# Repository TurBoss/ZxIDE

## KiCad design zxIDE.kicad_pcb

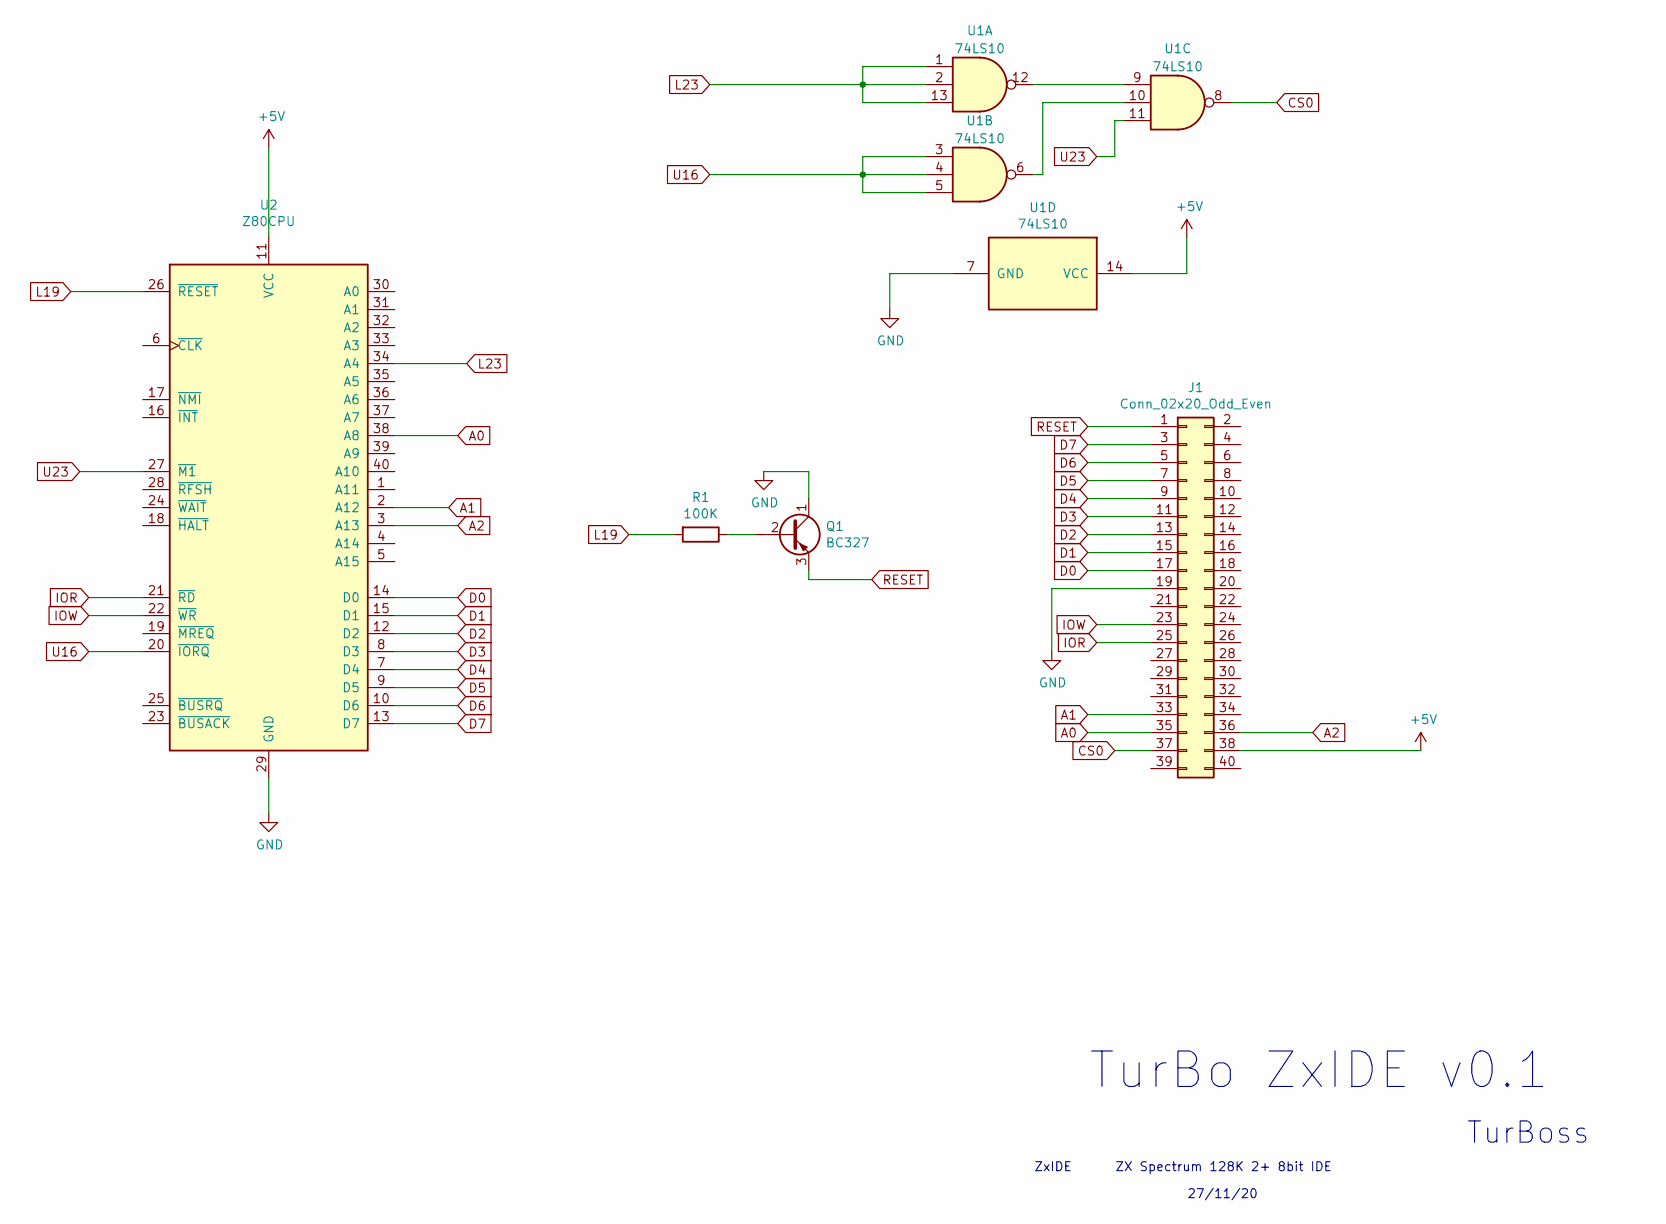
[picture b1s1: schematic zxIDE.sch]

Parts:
J1: Conn_02x20_Odd_Even; IDC-Header_2x20_P2.54mm_Vertical
Q1: BC327; TO-92_Inline
R1: 100K; R_Axial_DIN0207_L6.3mm_D2.5mm_P15.24mm_Horizontal
U1: 74LS10; DIP-14_W7.62mm_Socket_LongPads
U2: Z80CPU; DIP-40_W15.24mm_Socket_LongPads

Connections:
+5V: J1.38, U1.14 (VCC), U2.11 (VCC)
A0: J1.35, U2.38 (A8)
A1: J1.33, U2.2 (A12)
A2: J1.36, U2.3 (A13)
CS0: J1.37, U1.8
D0: J1.17, U2.14 (D0)
D1: J1.15, U2.15 (D1)
D2: J1.13, U2.12 (D2)
D3: J1.11, U2.8 (D3)
D4: J1.9, U2.7 (D4)
D5: J1.7, U2.9 (D5)
D6: J1.5, U2.10 (D6)
D7: J1.3, U2.13 (D7)
GND: J1.19, Q1.1 (C), U1.7 (GND), U2.29 (GND)
IOR: J1.25, U2.21 (~RD~)
IOW: J1.23, U2.22 (~WR~)
L19: R1.2, U2.26 (~RESET~)
L23: U1.1, U1.2, U1.13, U2.34 (A4)
unnamed: Q1.2 (B), R1.1
unnamed: U1.6, U1.10
unnamed: U1.9, U1.12
RESET: J1.1, Q1.3 (E)
U16: U1.3, U1.4, U1.5, U2.20 (~IORQ~)
U23: U1.11, U2.27 (~M1~)

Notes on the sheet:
TurBo ZxIDE v0.1
ZxIDE
27/11/20
TurBoss
ZX Spectrum 128K 2+ 8bit IDE

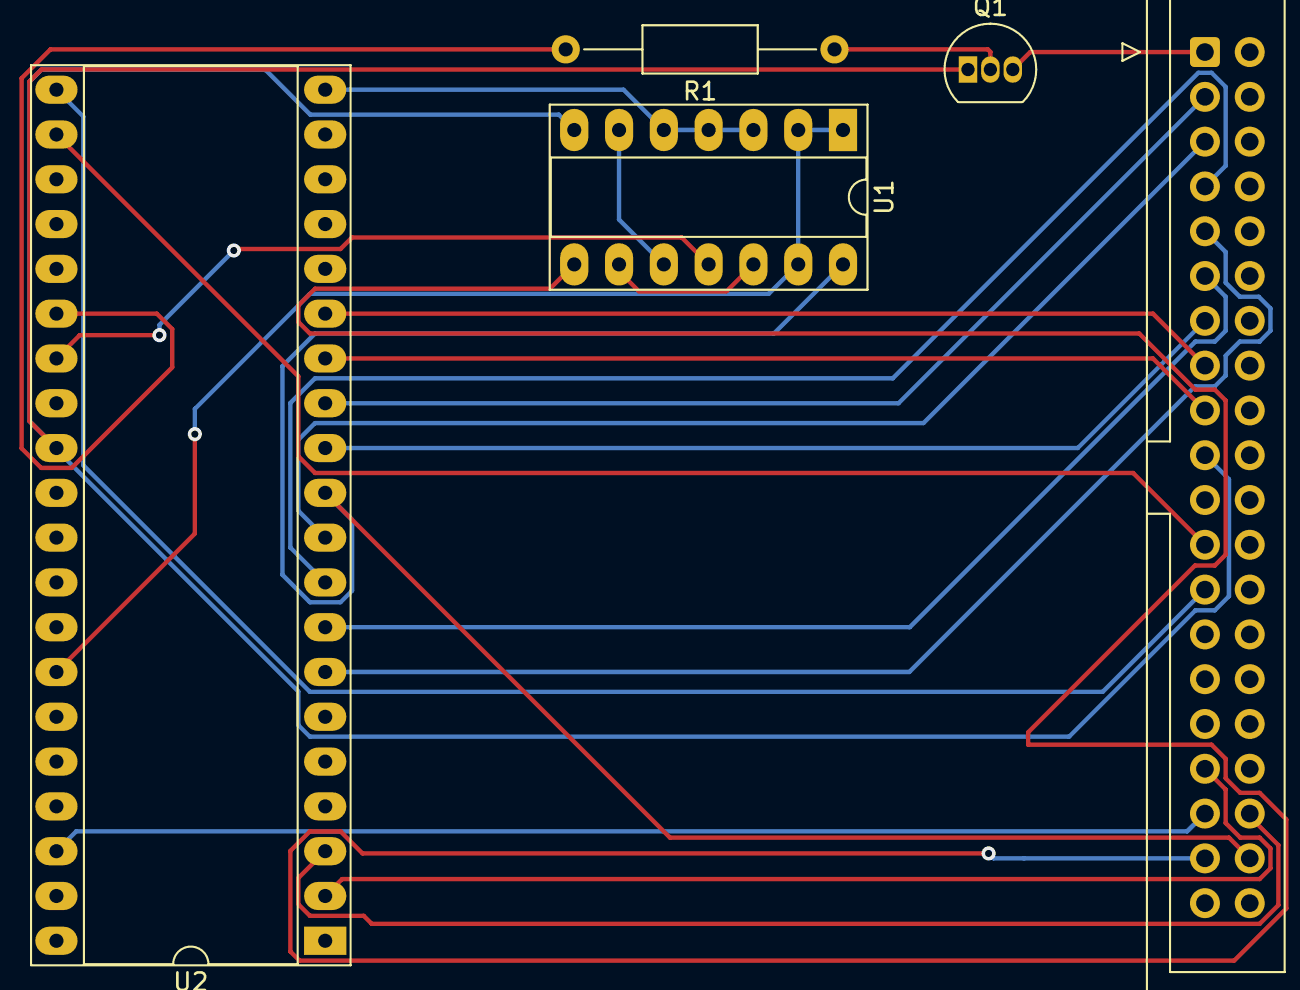
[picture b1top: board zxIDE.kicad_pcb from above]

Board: 2 copper layers, 5 parts (0 on the bottom side), 24 nets.

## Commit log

2020-11-27 Add Files
2020-11-27 add schematics in pdf and some pictures
